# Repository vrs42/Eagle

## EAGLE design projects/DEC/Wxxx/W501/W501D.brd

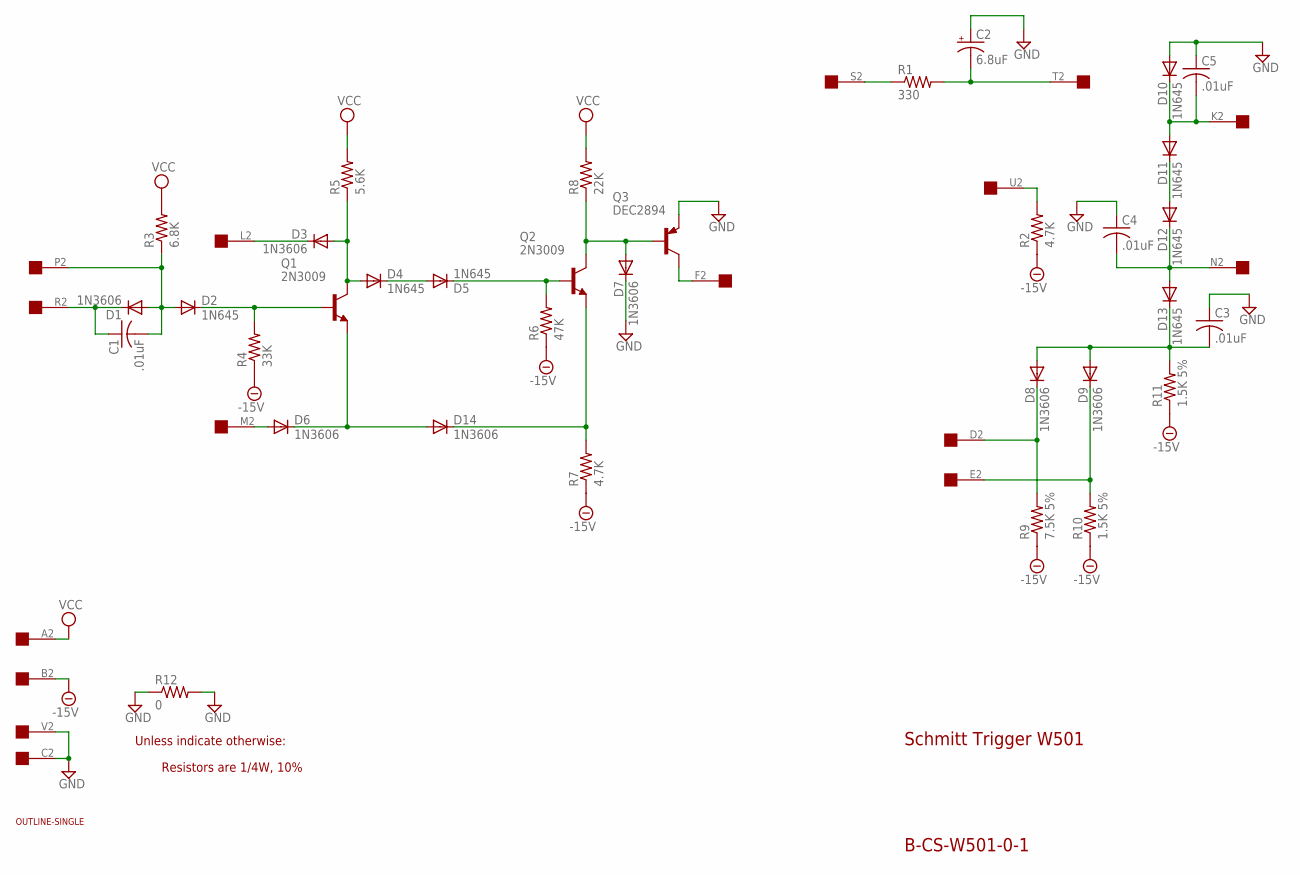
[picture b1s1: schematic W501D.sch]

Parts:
C1: .01uF; C075-032X103
C2: 6.8uF; E12-8
C3, C4, C5: .01uF; C063-025X075
D1, D3, D6, D7, D8, D9, D14: 1N3606; DO35-10
D2, D4, D5, D10, D11, D12, D13: 1N645; DO35-10
EDGE: EDGE-1; EDGE-CON1
Q1, Q2: 2N3009; TO5
Q3: DEC2894; TO39
R1: 330; 0207/10
R2, R7: 4.7K; 0207/10
R3: 6.8K; 0207/10
R4: 33K; 0207/10
R5: 5.6K; 0207/10
R6: 47K; 0207/10
R8: 22K; 0207/10
R9: 7.5K 5%; 0207/10
R10, R11: 1.5K 5%; 0207/10
R12: 0; 0207/10
U$1: OUTLINE-SINGLE; SINGLE

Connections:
-15V: EDGE.B2, R2.1, R4.1, R6.1, R7.1, R9.1, R10.1, R11.1
GND: C2.+, C3.1, C4.1, C5.1, D7.C, D10.A, EDGE.C2, EDGE.V2, Q3.1 (E), R12.1, R12.2
unnamed: C2.-, EDGE.T2, R1.2
unnamed: EDGE.S2, R1.1
unnamed: C5.2, D10.C, D11.A, EDGE.K2
unnamed: D11.C, D12.A
unnamed: C4.2, D12.C, D13.A, EDGE.N2
unnamed: C3.2, D8.A, D9.A, D13.C, R11.2
unnamed: D8.C, EDGE.D2, R9.2
unnamed: D9.C, EDGE.E2, R10.2
unnamed: EDGE.U2, R2.2
unnamed: EDGE.F2, Q3.3 (C)
unnamed: D7.A, Q2.3 (C), Q3.2 (B), R8.1
unnamed: D14.C, Q2.1 (E), R7.2
unnamed: D6.C, D14.A, Q1.1 (E)
unnamed: D3.A, D4.A, Q1.3 (C), R5.1
unnamed: D5.C, Q2.2 (B), R6.2
unnamed: D3.C, EDGE.L2
unnamed: D6.A, EDGE.M2
unnamed: C1.2, D1.A, D2.A, EDGE.P2, R3.1
unnamed: C1.1, D1.C, EDGE.R2
unnamed: D2.C, Q1.2 (B), R4.2
unnamed: D4.C, D5.A
VCC: EDGE.A2, R3.2, R5.2, R8.2

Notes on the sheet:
Schmitt Trigger W501
Resistors are 1/4W, 10%
B-CS-W501-0-1
Unless indicate otherwise:

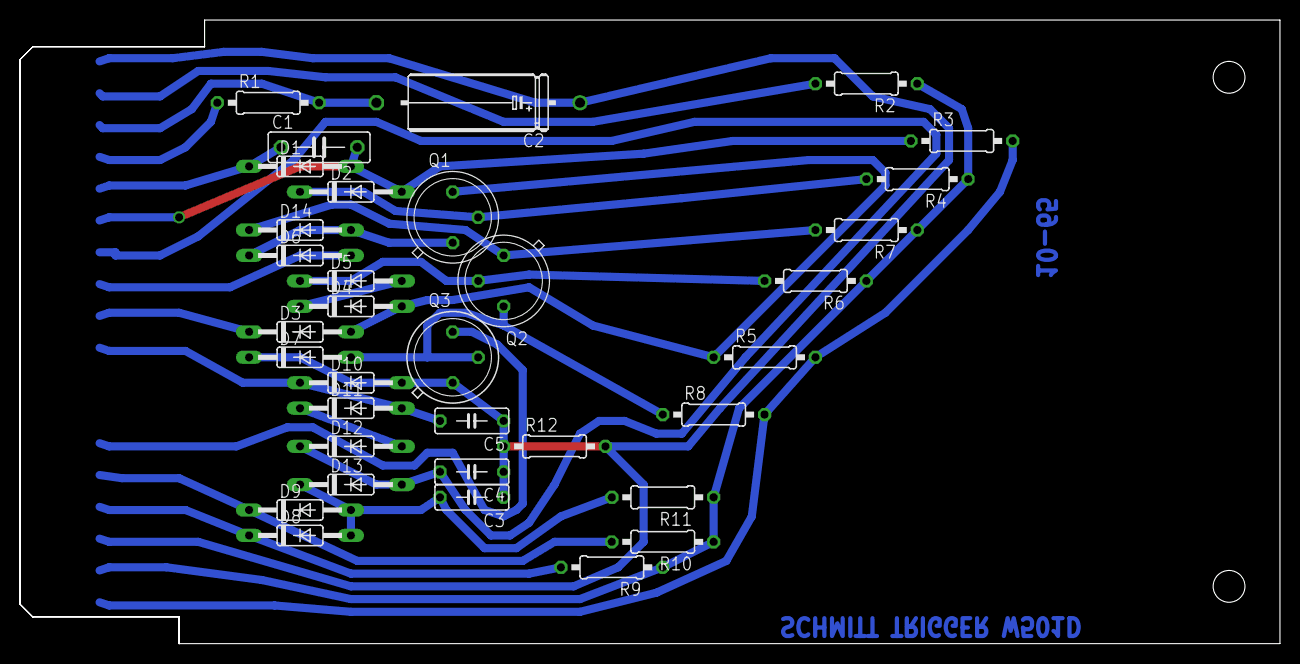
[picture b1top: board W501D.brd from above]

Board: 2 copper layers, 125.7 x 62.2 mm, 36 parts (0 on the bottom side), 24 nets.

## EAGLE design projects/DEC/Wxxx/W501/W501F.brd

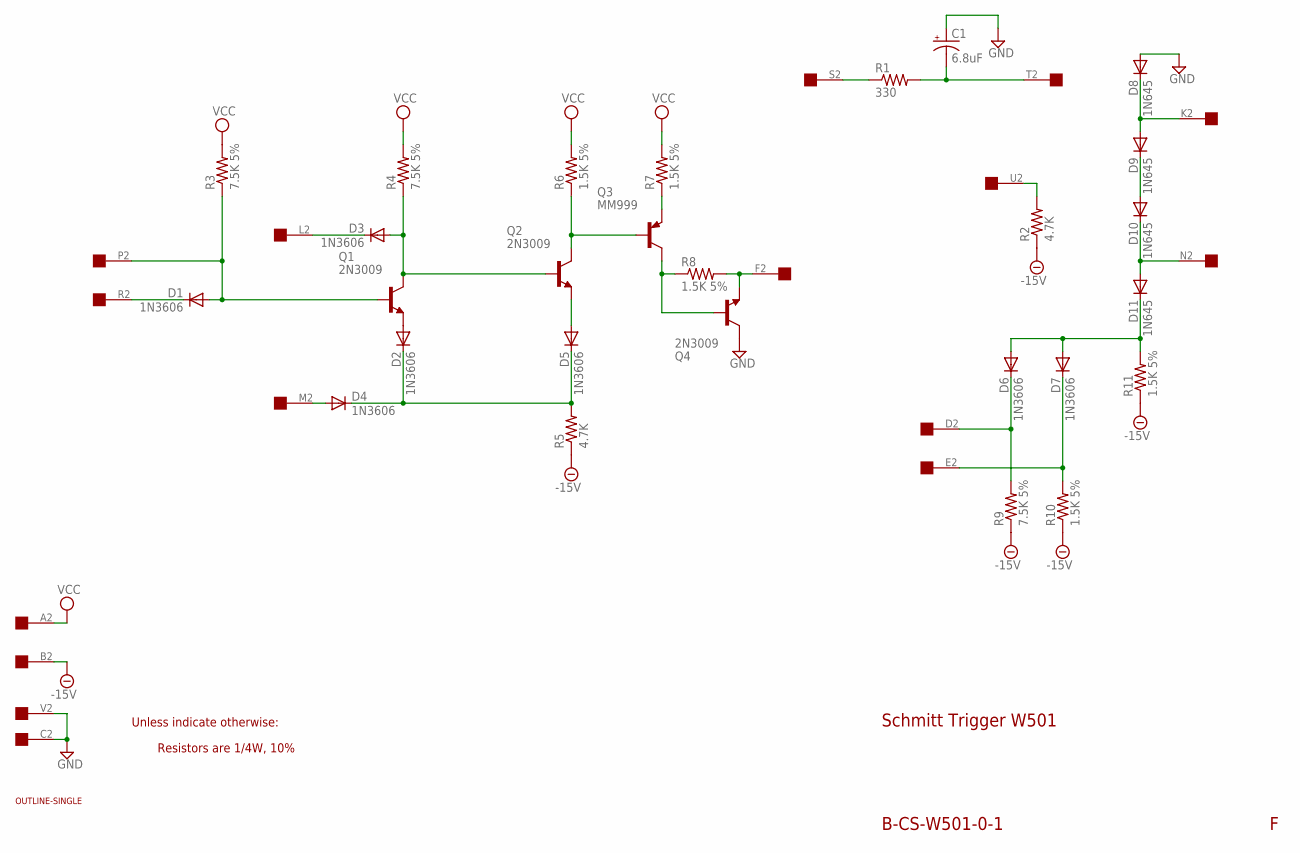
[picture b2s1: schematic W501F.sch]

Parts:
C1: 6.8uF; E15-5
D1, D2, D3, D4, D5, D6, D7: 1N3606; DO35-10
D8, D9, D10, D11: 1N645; DO35-10
EDGE: EDGE-1; EDGE-CON1
Q1, Q2, Q4: 2N3009; TO5
Q3: MM999; TO39
R1: 330; 0207/10
R2, R5: 4.7K; 0207/10
R3, R4, R9: 7.5K 5%; 0207/10
R6, R7, R8, R10, R11: 1.5K 5%; 0207/10
U$1: OUTLINE-SINGLE; SINGLE

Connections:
-15V: EDGE.B2, R2.1, R5.1, R9.1, R10.1, R11.1
GND: C1.+, D8.A, EDGE.C2, EDGE.V2, Q4.3 (C)
unnamed: Q3.1 (E), R7.1
unnamed: C1.-, EDGE.T2, R1.2
unnamed: EDGE.S2, R1.1
unnamed: D8.C, D9.A, EDGE.K2
unnamed: D9.C, D10.A
unnamed: D10.C, D11.A, EDGE.N2
unnamed: D6.A, D7.A, D11.C, R11.2
unnamed: D6.C, EDGE.D2, R9.2
unnamed: D7.C, EDGE.E2, R10.2
unnamed: EDGE.U2, R2.2
unnamed: EDGE.F2, Q4.1 (E), R8.2
unnamed: Q3.3 (C), Q4.2 (B), R8.1
unnamed: Q2.3 (C), Q3.2 (B), R6.1
unnamed: D5.A, Q2.1 (E)
unnamed: D2.C, D4.C, D5.C, R5.2
unnamed: D2.A, Q1.1 (E)
unnamed: D3.A, Q1.3 (C), Q2.2 (B), R4.1
unnamed: D3.C, EDGE.L2
unnamed: D4.A, EDGE.M2
unnamed: D1.A, EDGE.P2, Q1.2 (B), R3.1
unnamed: D1.C, EDGE.R2
VCC: EDGE.A2, R3.2, R4.2, R6.2, R7.2

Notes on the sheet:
Schmitt Trigger W501
Resistors are 1/4W, 10%
B-CS-W501-0-1
Unless indicate otherwise:

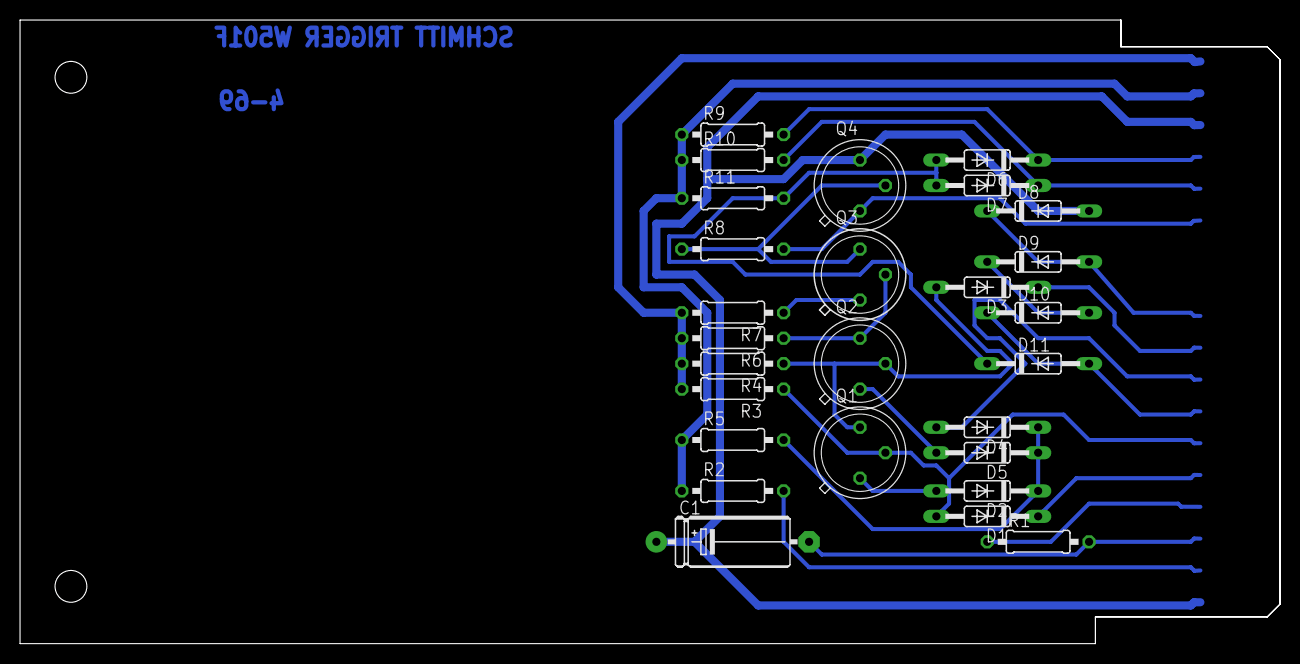
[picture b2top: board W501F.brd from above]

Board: 2 copper layers, 125.7 x 62.2 mm, 29 parts (0 on the bottom side), 24 nets.

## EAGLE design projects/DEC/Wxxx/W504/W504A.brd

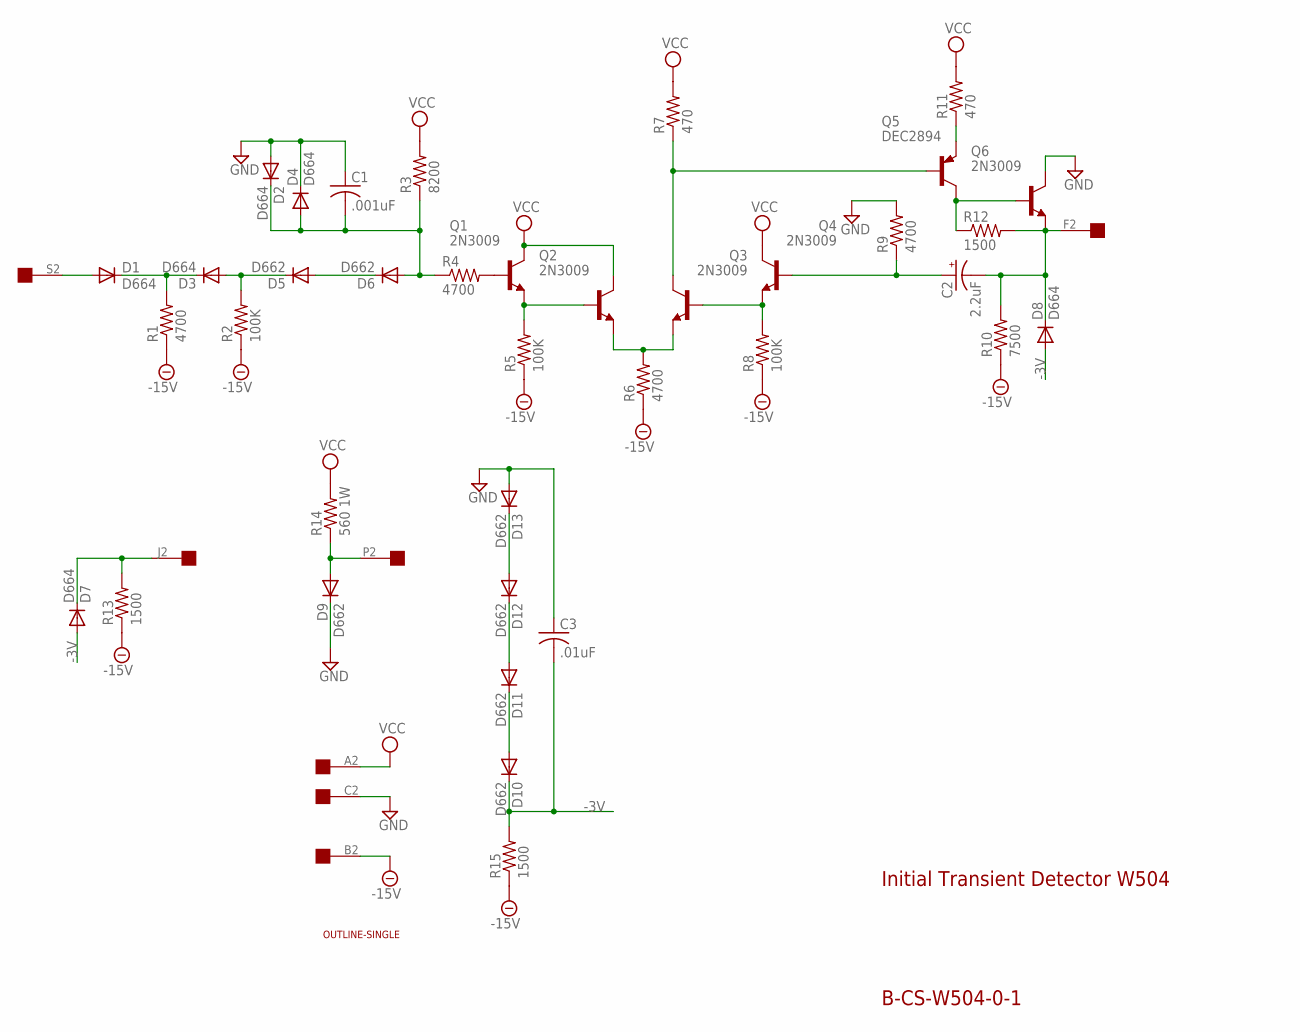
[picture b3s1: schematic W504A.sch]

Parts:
C1: .001uF; C150-054X183
C2: 2.2uF; E12-4
C3: .01uF; C150-054X183
D1, D2, D3, D4, D7, D8: D664; DO35-10
D5, D6, D9, D10, D11, D12, D13: D662; DO35-10
Q1, Q2, Q3, Q4, Q6: 2N3009; TO5
Q5: DEC2894; TO5
R1, R4, R6, R9: 4700; 0207/10
R2, R5, R8: 100K; 0207/10
R3: 8200; 0207/10
R7, R11: 470; 0207/10
R10: 7500; 0207/10
R12, R13, R15: 1500; 0207/10
R14: 560 1W; 0617/22
U$1: OUTLINE-SINGLE; SINGLE
U$2: EDGE-1; EDGE-CON1

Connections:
-3V: C3.2, D7.A, D8.A, D10.C, R15.2
-15V: R1.1, R2.1, R5.1, R6.1, R8.1, R10.1, R13.1, R15.1, U$2.B2
GND: C1.1, C3.1, D2.A, D4.C, D9.C, D13.A, Q6.3 (C), R9.2, U$2.C2
unnamed: D1.C, D3.C, R1.2
unnamed: D3.A, D5.C, R2.2
unnamed: D5.A, D6.C
unnamed: C1.2, D2.C, D4.A, D6.A, R3.1, R4.1
unnamed: Q1.1 (E), Q2.2 (B), R5.2
unnamed: Q1.2 (B), R4.2
unnamed: Q2.1 (E), Q3.1 (E), R6.2
unnamed: Q3.3 (C), Q5.2 (B), R7.1
unnamed: Q3.2 (B), Q4.1 (E), R8.2
unnamed: C2.+, Q4.2 (B), R9.1
unnamed: C2.-, D8.C, Q6.1 (E), R10.2, R12.2, U$2.F2
unnamed: Q5.1 (E), R11.1
unnamed: Q5.3 (C), Q6.2 (B), R12.1
unnamed: D7.C, R13.2, U$2.J2
unnamed: D9.A, R14.1, U$2.P2
unnamed: D12.A, D13.C
unnamed: D11.A, D12.C
unnamed: D10.A, D11.C
S2: D1.A, U$2.S2
VCC: Q1.3 (C), Q2.3 (C), Q4.3 (C), R3.2, R7.2, R11.2, R14.2, U$2.A2

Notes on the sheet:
Initial Transient Detector W504
B-CS-W504-0-1

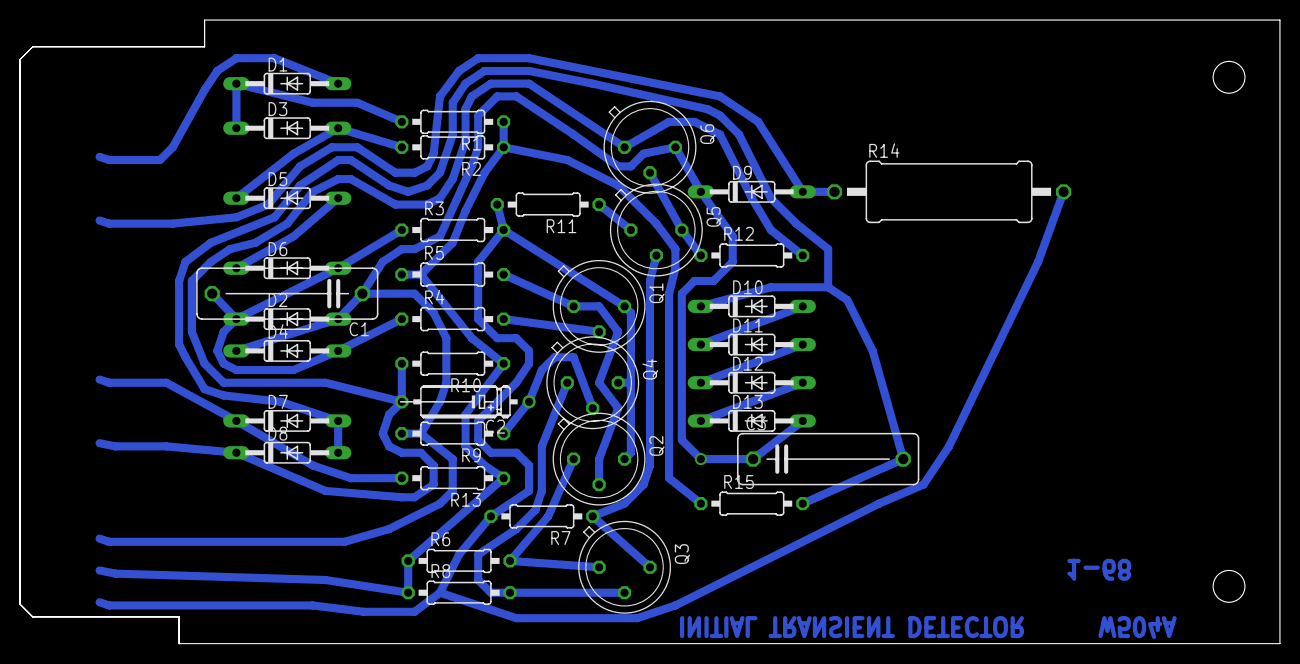
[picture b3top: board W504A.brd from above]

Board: 2 copper layers, 125.7 x 62.2 mm, 39 parts (0 on the bottom side), 23 nets.

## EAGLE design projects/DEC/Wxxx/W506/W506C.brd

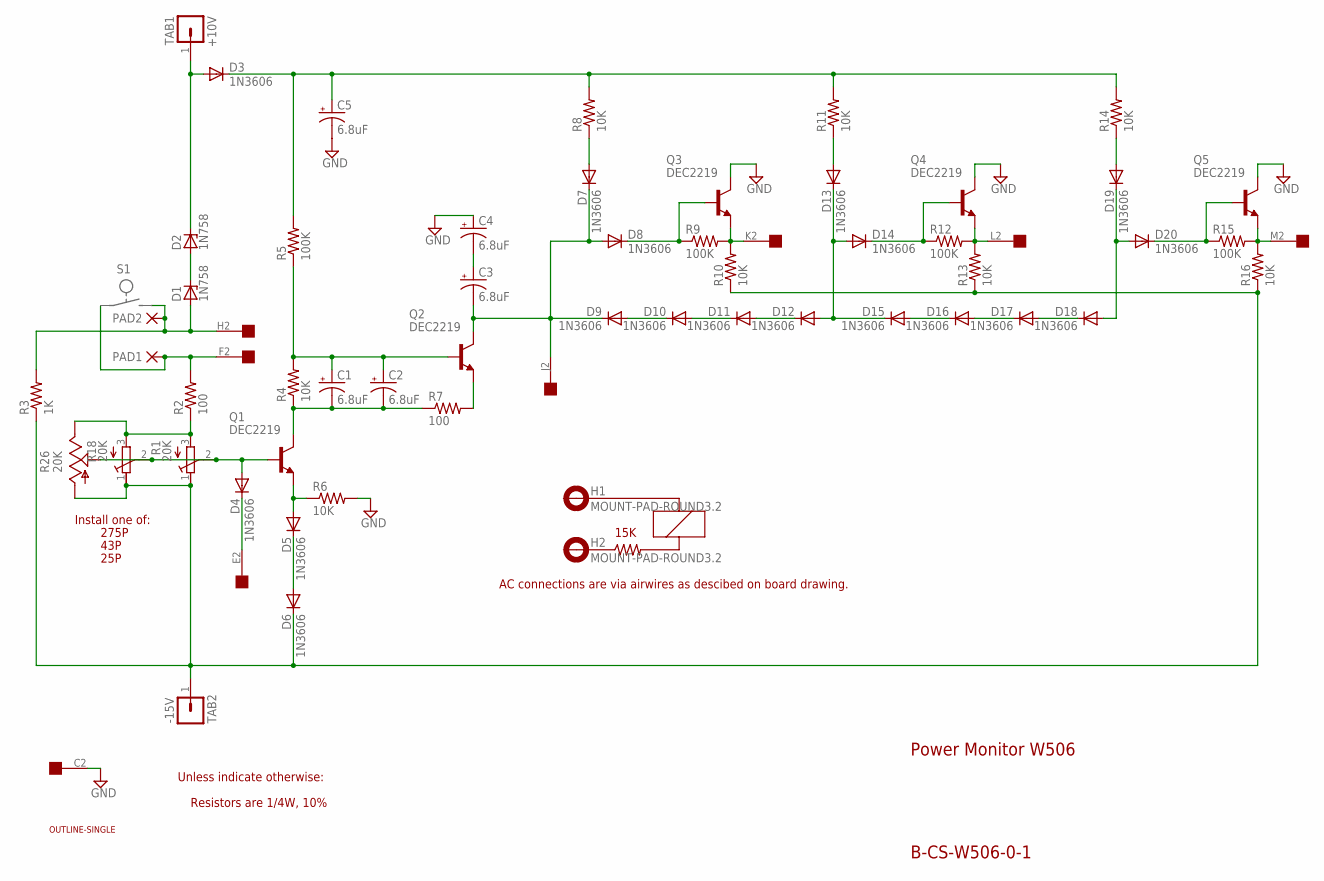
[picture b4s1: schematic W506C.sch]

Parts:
C1, C2, C3, C4, C5: 6.8uF; E15-5
D1, D2: 1N758; DO35Z10
D3, D4, D5, D6, D7, D8, D9, D10, D11, D12, D13, D14, D15, D16, D17, D18, D19, D20: 1N3606; DO35-10
EDGE: EDGE-1; EDGE-CON1
H1, H2: MOUNT-PAD-ROUND3.2; 3,2-PAD
PAD1, PAD2: PAD-0320; 0320
Q1, Q2, Q3, Q4, Q5: DEC2219; TO5
R1: 20K; 3006Y
R2, R7: 100; 0207/10
R3: 1K; 0207/10
R4, R6, R8, R10, R11, R13, R14, R16: 10K; 0207/10
R5, R9, R12, R15: 100K; 0207/10
R18: 20K; RTRIM43P
R26: 20K; B25P
TAB1: +10V; SPADELUG
TAB2: -15V; SPADELUG
U$1: OUTLINE-SINGLE; SINGLE

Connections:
+10V: D2.C, D3.A, TAB1.1
-15V: D6.C, R1.1 (A), R3.1, R10.1, R13.1, R16.1, R18.1 (E), R26.A, TAB2.1
GND: C4.+, C5.-, EDGE.C2, Q3.3 (C), Q4.3 (C), Q5.3 (C), R6.2
unnamed: R1.3 (E), R2.1, R18.3 (A), R26.E
unnamed: D1.C, D2.A
unnamed: D1.A, EDGE.H2, PAD2.P$1, R3.2
unnamed: C1.-, C2.-, Q1.3 (C), R4.1, R7.1
unnamed: D4.A, Q1.2 (B), R1.2 (S), R18.2 (S), R26.S
unnamed: D4.C, EDGE.E2
unnamed: D5.C, D6.A
unnamed: D5.A, Q1.1 (E), R6.1
unnamed: C5.+, D3.C, R5.2, R8.2, R11.2, R14.2
unnamed: C1.+, C2.+, Q2.2 (B), R4.2, R5.1
unnamed: EDGE.F2, PAD1.P$1, R2.2
unnamed: Q2.1 (E), R7.2
unnamed: C3.+, C4.-
unnamed: EDGE.M2, Q5.1 (E), R15.2, R16.2
unnamed: C3.-, D7.C, D8.A, D9.C, EDGE.J2, Q2.3 (C)
unnamed: D9.A, D10.C
unnamed: D10.A, D11.C
unnamed: D11.A, D12.C
unnamed: D7.A, R8.1
unnamed: D8.C, Q3.2 (B), R9.1
unnamed: EDGE.K2, Q3.1 (E), R9.2, R10.2
unnamed: D12.A, D13.C, D14.A, D15.C
unnamed: D13.A, R11.1
unnamed: EDGE.L2, Q4.1 (E), R12.2, R13.2
unnamed: D14.C, Q4.2 (B), R12.1
unnamed: D15.A, D16.C
unnamed: D16.A, D17.C
unnamed: D17.A, D18.C
unnamed: D20.C, Q5.2 (B), R15.1
unnamed: D19.A, R14.1
unnamed: D18.A, D19.C, D20.A

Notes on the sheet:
Power Monitor W506
Resistors are 1/4W, 10%
B-CS-W506-0-1
Unless indicate otherwise:
Install one of:
275P
43P
25P
AC connections are via airwires as descibed on board drawing.
15K

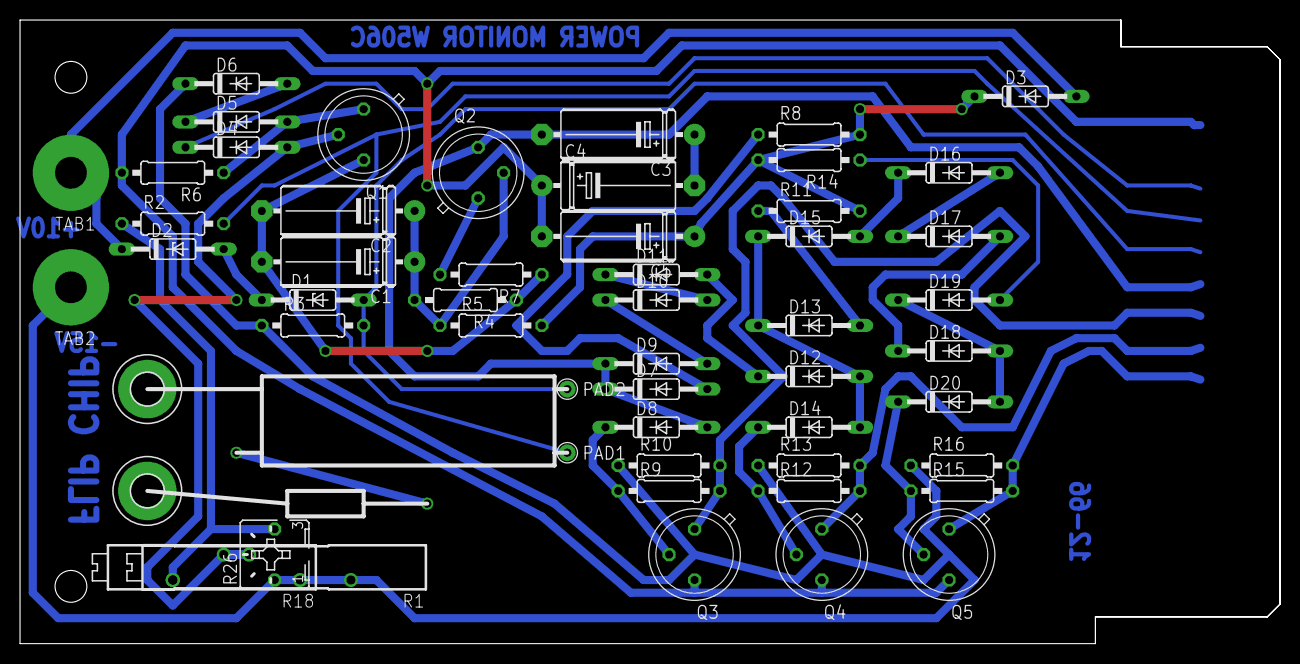
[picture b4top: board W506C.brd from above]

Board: 2 copper layers, 125.7 x 62.2 mm, 57 parts (1 on the bottom side), 34 nets.

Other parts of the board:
U$2: FLIPCHIP
